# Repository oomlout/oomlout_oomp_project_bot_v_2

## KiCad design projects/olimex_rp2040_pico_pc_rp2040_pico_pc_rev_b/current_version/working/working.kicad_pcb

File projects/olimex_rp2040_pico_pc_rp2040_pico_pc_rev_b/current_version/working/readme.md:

# rp2040_pico_pc
 
## summary 
* id: olimex_rp2040_pico_pc_rp2040_pico_pc_rev_b
* user: olimex
* name: rp2040_pico_pc
* board: rp2040_pico_pc_rev_b
* repo: https://github.com/OLIMEX/RP2040-PICO-PC
* src_file_repo_kicad_pcb: HARDWARE/RP2040-PICO-PC hardware revision B/RP2040-PICO-PC_rev_B.kicad_pcb
* src_file_repo_kicad_pcb_link: https://github.com/OLIMEX/RP2040-PICO-PC/tree/main/HARDWARE/RP2040-PICO-PC hardware revision B/RP2040-PICO-PC_rev_B.kicad_pcb

* src_file_repo_sch: HARDWARE/RP2040-PICO-PC hardware revision B/RP2040-PICO-PC_rev_B.sch
* src_file_repo_sch_link: https://github.com/OLIMEX/RP2040-PICO-PC/tree/main/HARDWARE/RP2040-PICO-PC hardware revision B/RP2040-PICO-PC_rev_B.sch
* full details link: https://github.com/oomlout/oomlout_oomp_project_bot_v_2/tree/main/projects/olimex_rp2040_pico_pc_rp2040_pico_pc_rev_b/current_version/working

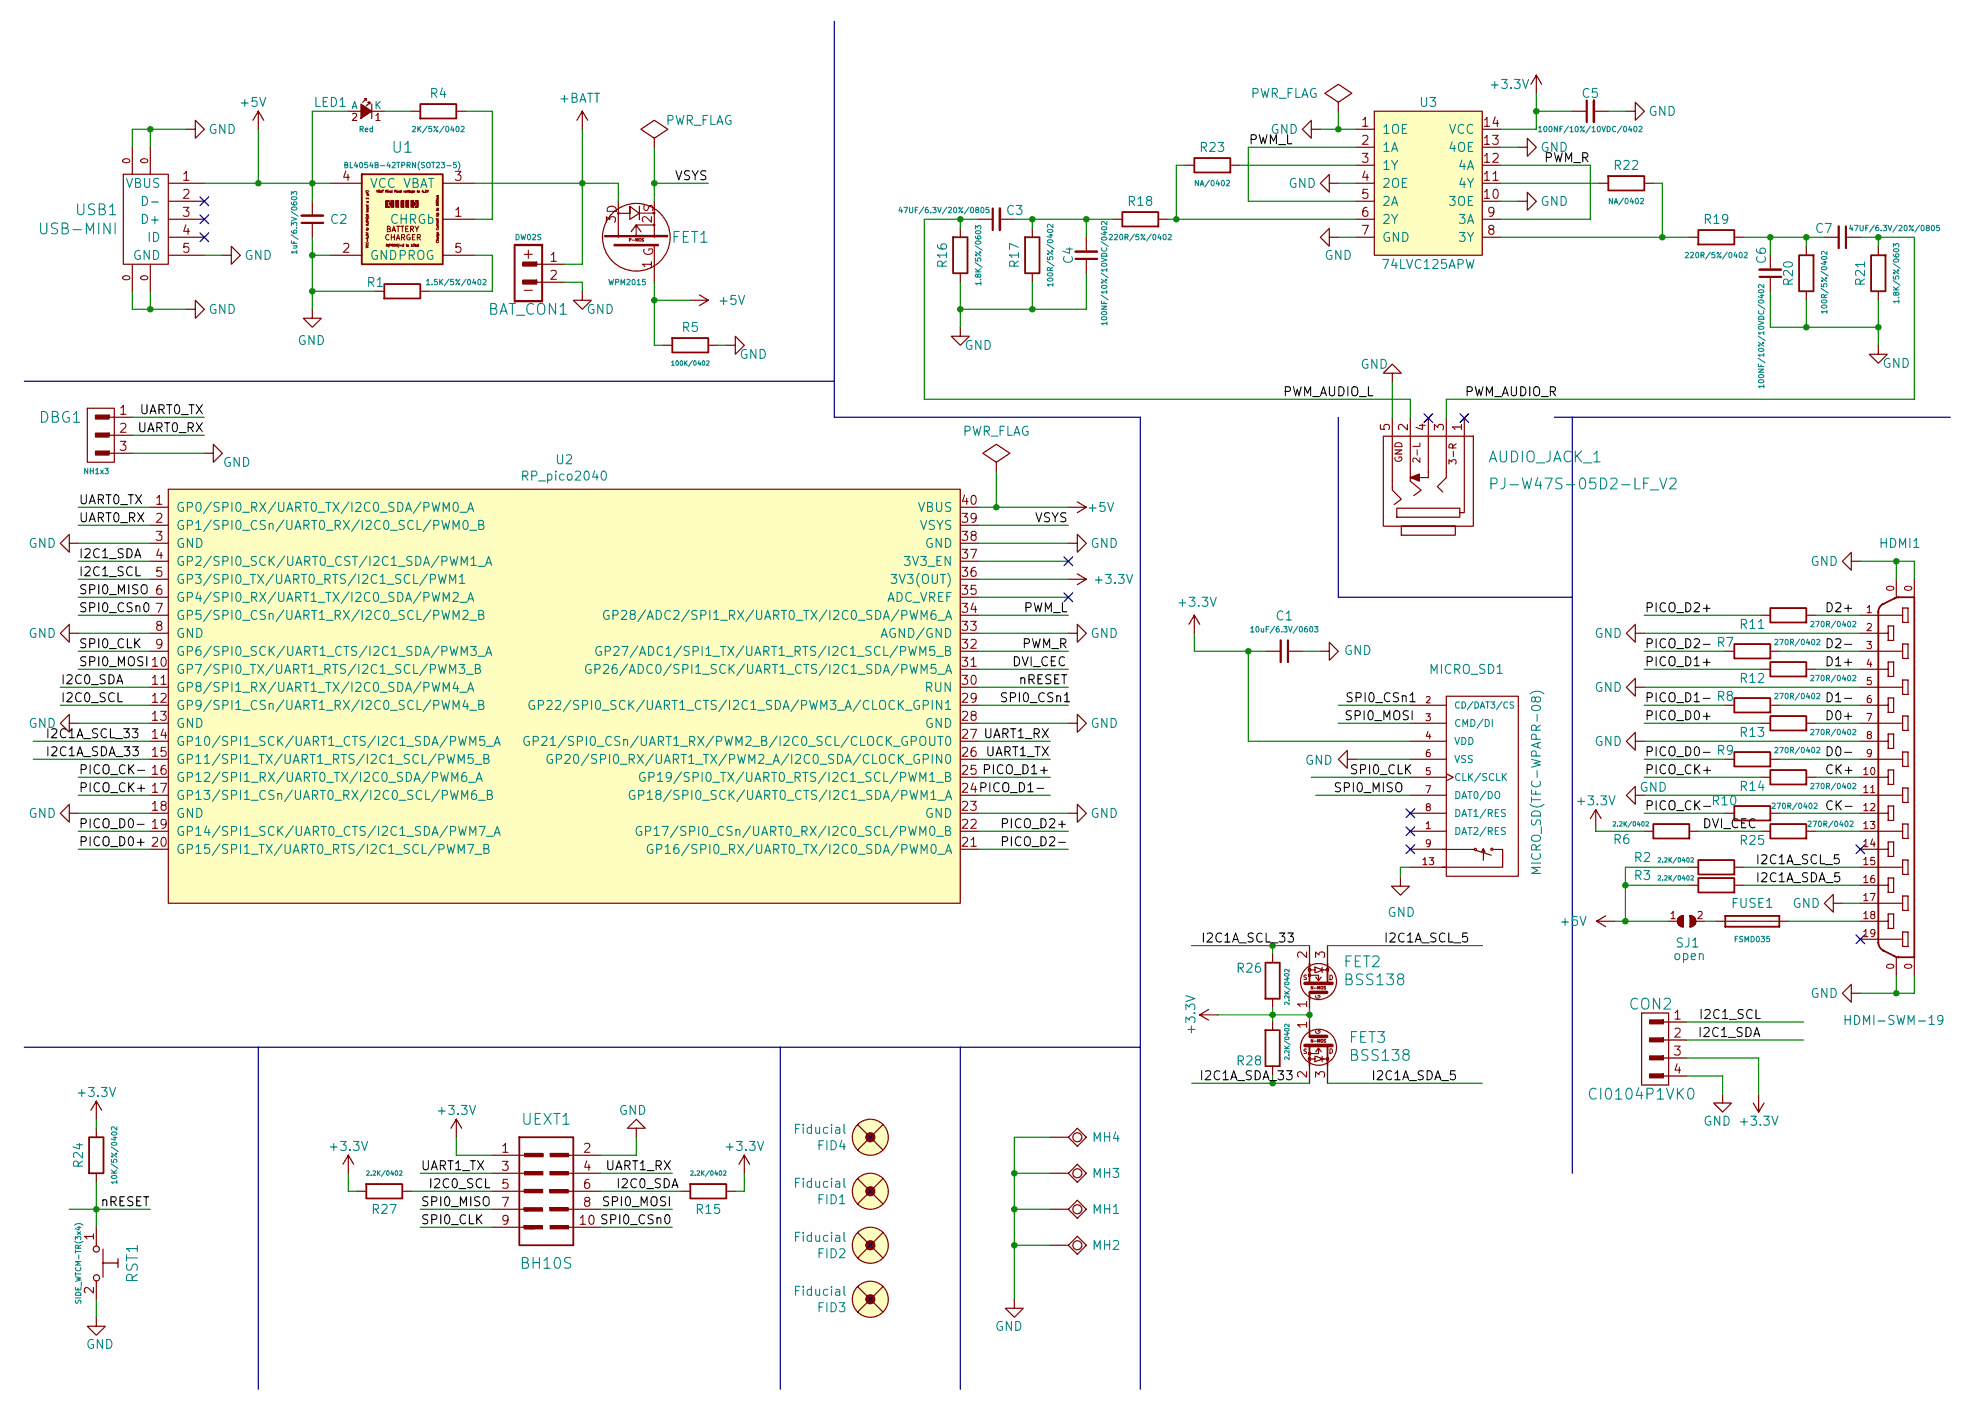
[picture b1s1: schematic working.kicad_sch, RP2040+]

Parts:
AUDIO_JACK_1: PJ-W47S-05D2-LF_V2; PJ-W47S-05D2-LF_5PIN_V2
BAT_CON1: DW02S; LIPO_BAT_VERTICAL_DW02S
C1: 10uF/6.3V/0603; C_0603_5MIL_DWS
C2: 1uF/6.3V/0603; C_0603_5MIL_DWS
C3, C7: 47UF/6.3V/20%/0805; C_0805_5MIL_DWS
C4, C5, C6: 100NF/10%/10VDC/0402; C_0402_5MIL_DWS
CON2: CI0104P1VK0; CL0104PV1K0
DBG1: NH1x3; HN1x3
FET1: WPM2015; SOT23
FET2, FET3: BSS138; SOT23
FID1, FID2, FID3, FID4: Fiducial; Fiducial1x3
FUSE1: FSMD035; FUSE-1206
HDMI1: HDMI-SWM-19; HDMI-SWM-19-TEST
LED1: Red; LED_0603_KA
MH1, MH2, MH3, MH4: Mounting_hole_Shield_3.3mm
MICRO_SD1: MICRO_SD(TFC-WPAPR-08); TFC-WPAPR-08
R1: 1.5K/5%/0402; R_0402_5MIL_DWS
R2, R3, R6, R15, R26, R27, R28: 2.2K/0402; R_0402_5MIL_DWS
R4: 2K/5%/0402; R_0402_5MIL_DWS
R5: 100K/0402; R_0402_5MIL_DWS
R7, R8, R9, R10, R11, R12, R13, R14, R25: 270R/0402; R_0402_5MIL_DWS
R16, R21: 1.8K/5%/0603; R_0603_5MIL_DWS
R17, R20: 100R/5%/0402; R_0402_5MIL_DWS
R18, R19: 220R/5%/0402; R_0402_5MIL_DWS
R22, R23: NA/0402; R_0402_5MIL_DWS
R24: 10K/5%/0402; R_0402_5MIL_DWS
RST1: SIDE_WTCM-TR(3x4); TSW34-W16PR-220
SJ1: open; SJ_1_SMALLER
U1: BL4054B-42TPRN(SOT23-5); SOT-23-5
U2: RP_pico2040; RP_Pico2040
U3: 74LVC125APW; 74LVC125A(TSSOP14-14_leads-4.4mm_body_width-SOT402-1)
UEXT1: BH10S
USB1: USB-MINI; USB-MICRO_MISB-SWMM-5B_LF

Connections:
+3V3: C1.2, C5.1, CON2.3, FET2.1 (G), FET3.1 (G), MICRO_SD1.4 (VDD), R6.1, R15.1, R24.1, R26.2, R27.2, R28.2, U2.36 (3V3(OUT)), U3.14 (VCC), UEXT1.1
+5V: C2.2, FET1.1, LED1.2 (A), R2.1, R3.1, R5.2, SJ1.1, U1.4 (VCC), U2.40 (VBUS), USB1.1 (VBUS)
+BATT: BAT_CON1.1, FET1.3, U1.3 (VBAT)
/CK+: HDMI1.10, R14.2
/CK-: HDMI1.12, R10.2
/D0+: HDMI1.7, R13.2
/D0-: HDMI1.9, R9.2
/D1+: HDMI1.4, R12.2
/D1-: HDMI1.6, R8.2
/D2+: HDMI1.1, R11.2
/D2-: HDMI1.3, R7.2
/DVI_CEC: R6.2, R25.1, U2.31 (GP26/ADC0/SPI1_SCK/UART1_CTS/I2C1_SDA/P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)
/I2C0_SCL: R27.1, U2.12 (GP9/SPI1_CSn/UART1_RX/I2C0_SCL/PWM4_B), UEXT1.5
/I2C0_SDA: R15.2, U2.11 (GP8/SPI1_RX/UART1_TX/I2C0_SDA/PWM4_A), UEXT1.6
/I2C1A_SCL_5: FET2.3 (D), HDMI1.15, R2.2
/I2C1A_SCL_33: FET2.2 (S), R26.1, U2.14 (GP10/SPI1_SCK/UART1_CTS/I2C1_SDA/PWM5_A)
/I2C1A_SDA_5: FET3.3 (D), HDMI1.16, R3.2
/I2C1A_SDA_33: FET3.2 (S), R28.1, U2.15 (GP11/SPI1_TX/UART1_RTS/I2C1_SCL/PWM5_B)
/I2C1_SCL: CON2.1, U2.5 (GP3/SPI0_TX/UART0_RTS/I2C1_SCL/PWM1)
/I2C1_SDA: CON2.2, U2.4 (GP2/SPI0_SCK/UART0_CST/I2C1_SDA/PWM1_A)
/PICO_CK+: R14.1, U2.17 (GP13/SPI1_CSn/UART0_RX/I2C0_SCL/PWM6_B)
/PICO_CK-: R10.1, U2.16 (GP12/SPI1_RX/UART0_TX/I2C0_SDA/PWM6_A)
/PICO_D0+: R13.1, U2.20 (GP15/SPI1_TX/UART0_RTS/I2C1_SCL/PWM7_B)
/PICO_D0-: R9.1, U2.19 (GP14/SPI1_SCK/UART0_CTS/I2C1_SDA/PWM7_A)
/PICO_D1+: R12.1, U2.25 (GP19/SPI0_TX/UART0_RTS/I2C1_SCL/PWM1_B)
/PICO_D1-: R8.1, U2.24 (GP18/SPI0_SCK/UART0_CTS/I2C1_SDA/PWM1_A)
/PICO_D2+: R11.1, U2.22 (GP17/SPI0_CSn/UART0_RX/I2C0_SCL/PWM0_B)
/PICO_D2-: R7.1, U2.21 (GP16/SPI0_RX/UART0_TX/I2C0_SDA/PWM0_A)
/PWM_AUDIO_L: AUDIO_JACK_1.2, C3.1, R16.2
/PWM_AUDIO_R: AUDIO_JACK_1.3, C7.1, R21.2
/PWM_L: U2.34 (GP28/ADC2/SPI1_RX/UART0_TX/I2C0_SDA/PWM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), U3.2 (1A), U3.5 (2A)
/PWM_R: U2.32 (GP27/ADC1/SPI1_TX/UART1_RTS/I2C1_SCL/PW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), U3.9 (3A), U3.12 (4A)
/SPI0_CLK: MICRO_SD1.5 (CLK/SCLK), U2.9 (GP6/SPI0_SCK/UART1_CTS/I2C1_SDA/PWM3_A), UEXT1.9
/SPI0_CSn0: U2.7 (GP5/SPI0_CSn/UART1_RX/I2C0_SCL/PWM2_B), UEXT1.10
/SPI0_CSn1: MICRO_SD1.2 (CD/DAT3/CS), U2.29 (GP22/SPI0_SCK/UART1_CTS/I2C1_SDA/PWM3_A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)
/SPI0_MISO: MICRO_SD1.7 (DAT0/DO), U2.6 (GP4/SPI0_RX/UART1_TX/I2C0_SDA/PWM2_A), UEXT1.7
/SPI0_MOSI: MICRO_SD1.3 (CMD/DI), U2.10 (GP7/SPI0_TX/UART1_RTS/I2C1_SCL/PWM3_B), UEXT1.8
/UART0_RX: DBG1.2, U2.2 (GP1/SPI0_CSn/UART0_RX/I2C0_SCL/PWM0_B)
/UART0_TX: DBG1.1, U2.1 (GP0/SPI0_RX/UART0_TX/I2C0_SDA/PWM0_A)
/UART1_RX: U2.27 (GP21/SPI0_CSn/UART1_RX/PWM2_B/I2C0_SCL/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), UEXT1.4
/UART1_TX: U2.26 (GP20/SPI0_RX/UART1_TX/PWM2_A/I2C0_SDA/C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), UEXT1.3
/VSYS: FET1.2, U2.39 (VSYS)
/nRESET: R24.2, RST1.1, U2.30 (RUN)
GND: AUDIO_JACK_1.5, BAT_CON1.2, C1.1, C2.1, C4.1, C5.2, C6.1, CON2.4, DBG1.3, HDMI1.0 (20), HDMI1.2, HDMI1.5, HDMI1.8, HDMI1.11, HDMI1.17, MH1.GND1, MH2.GND1, MH3.GND1, MH4.GND1, MICRO_SD1.6 (VSS), MICRO_SD1.10, MICRO_SD1.11, MICRO_SD1.12, MICRO_SD1.13, R1.2, R5.1, R16.1, R17.1, R20.1, R21.1, RST1.2, U1.2 (GND), U2.3 (GND), U2.8 (GND), U2.13 (GND), U2.18 (GND), U2.23 (GND), U2.28 (GND), U2.33 (AGND/GND), U2.38 (GND), U3.1 (1OE), U3.4 (2OE), U3.7 (GND), U3.10 (3OE), U3.13 (4OE), UEXT1.2, USB1.0, USB1.5 (GND)
unnamed: C3.2, C4.2, R17.2, R18.1
unnamed: C6.2, C7.2, R19.1, R20.2
unnamed: FUSE1.1, SJ1.2
unnamed: FUSE1.2, HDMI1.18
unnamed: HDMI1.13, R25.2
unnamed: LED1.1 (K), R4.2
unnamed: R1.1, U1.5 (PROG)
unnamed: R4.1, U1.1 (CHRGb)
unnamed: R18.2, R23.1, U3.6 (2Y)
unnamed: R19.2, R22.1, U3.8 (3Y)
unnamed: R22.2, U3.11 (4Y)
unnamed: R23.2, U3.3 (1Y)

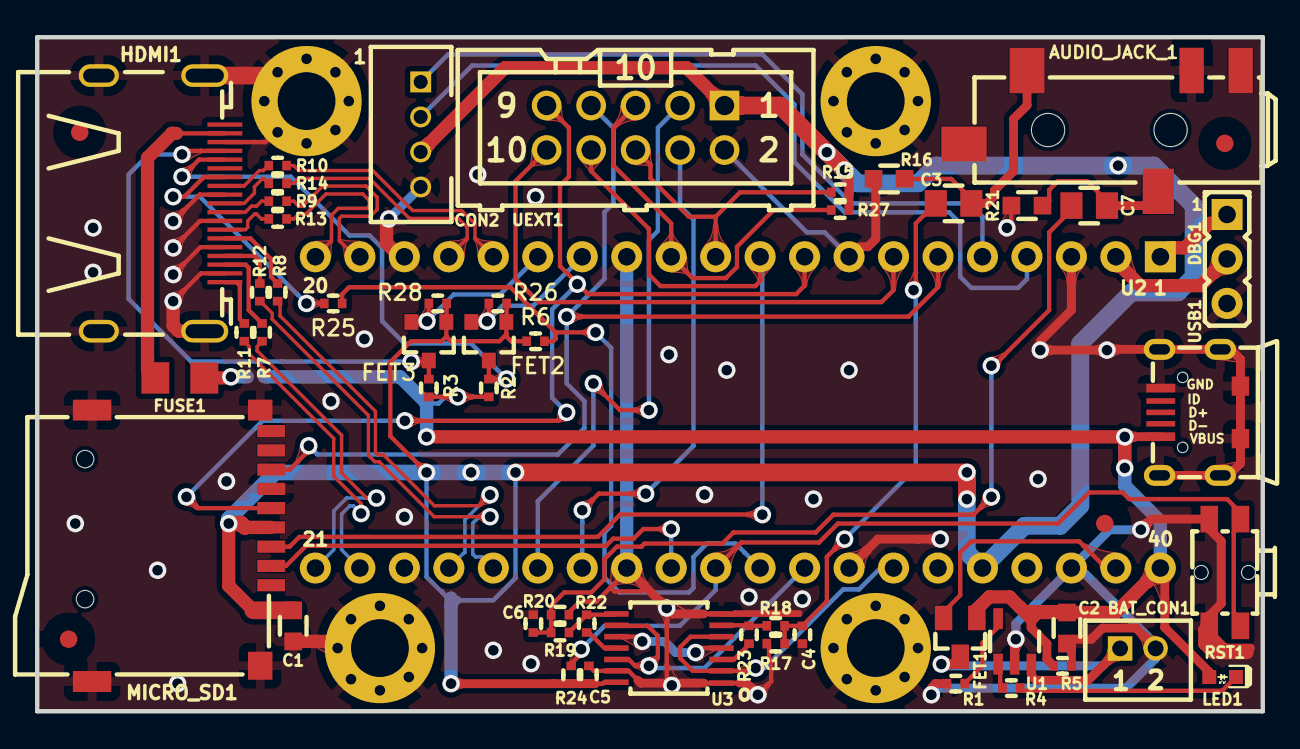
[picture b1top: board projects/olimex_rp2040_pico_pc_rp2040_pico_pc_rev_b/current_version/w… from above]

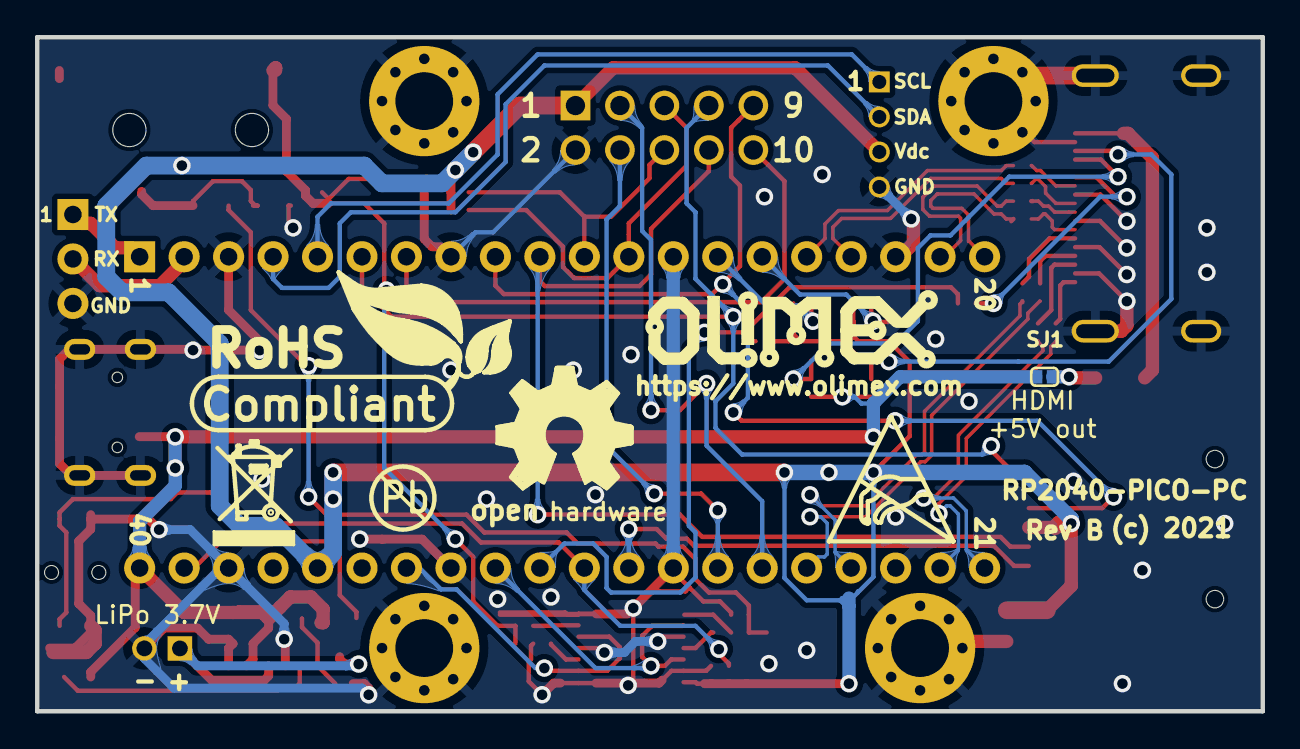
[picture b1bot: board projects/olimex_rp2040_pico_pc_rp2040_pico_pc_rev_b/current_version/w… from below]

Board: 2 copper layers, 70.0 x 38.5 mm, 67 parts (7 on the bottom side), 56 nets.

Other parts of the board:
Antistatic: Logo; LOGO_ANTISTATIC_1
OLIMEX_LOGO: Logo; OLIMEX_LOGO_TB
Open_Hardware: Logo; LOGO_OPENHARDWARE_8x8
PB_FREE: Logo; LOGO_PBFREE
Recycle_bin: logo; LOGO_RECYCLEBIN_1
RoHS_Complaint: Logo; LOGO_ROHS_1

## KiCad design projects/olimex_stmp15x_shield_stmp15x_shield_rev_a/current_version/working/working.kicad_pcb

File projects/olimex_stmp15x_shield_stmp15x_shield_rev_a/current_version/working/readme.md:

# stmp15x_shield
 
## summary 
* id: olimex_stmp15x_shield_stmp15x_shield_rev_a
* user: olimex
* name: stmp15x_shield
* board: stmp15x_shield_rev_a
* repo: https://github.com/OLIMEX/STMP15X-SHIELD
* src_file_repo_kicad_pcb: HARDWARE/STMP15x-SHIELD_Rev_A/STMP15x-SHIELD_Rev_A.kicad_pcb
* src_file_repo_kicad_pcb_link: https://github.com/OLIMEX/STMP15X-SHIELD/tree/main/HARDWARE/STMP15x-SHIELD_Rev_A/STMP15x-SHIELD_Rev_A.kicad_pcb

* src_file_repo_brd: HARDWARE/STMP15x-SHIELD_Rev_A/Extensions/A10-A20-OLINUXINO-MICRO_Extension_Rev_A_STMP15x-SHIELD_GPIO1_EXTENSION.brd
* src_file_repo_brd_link: https://github.com/OLIMEX/STMP15X-SHIELD/tree/main/HARDWARE/STMP15x-SHIELD_Rev_A/Extensions/A10-A20-OLINUXINO-MICRO_Extension_Rev_A_STMP15x-SHIELD_GPIO1_EXTENSION.brd
* src_file_repo_sch: HARDWARE/STMP15x-SHIELD_Rev_A/STMP15x-SHIELD_Rev_A.sch
* src_file_repo_sch_link: https://github.com/OLIMEX/STMP15X-SHIELD/tree/main/HARDWARE/STMP15x-SHIELD_Rev_A/STMP15x-SHIELD_Rev_A.sch
* full details link: https://github.com/oomlout/oomlout_oomp_project_bot_v_2/tree/main/projects/olimex_stmp15x_shield_stmp15x_shield_rev_a/current_version/working

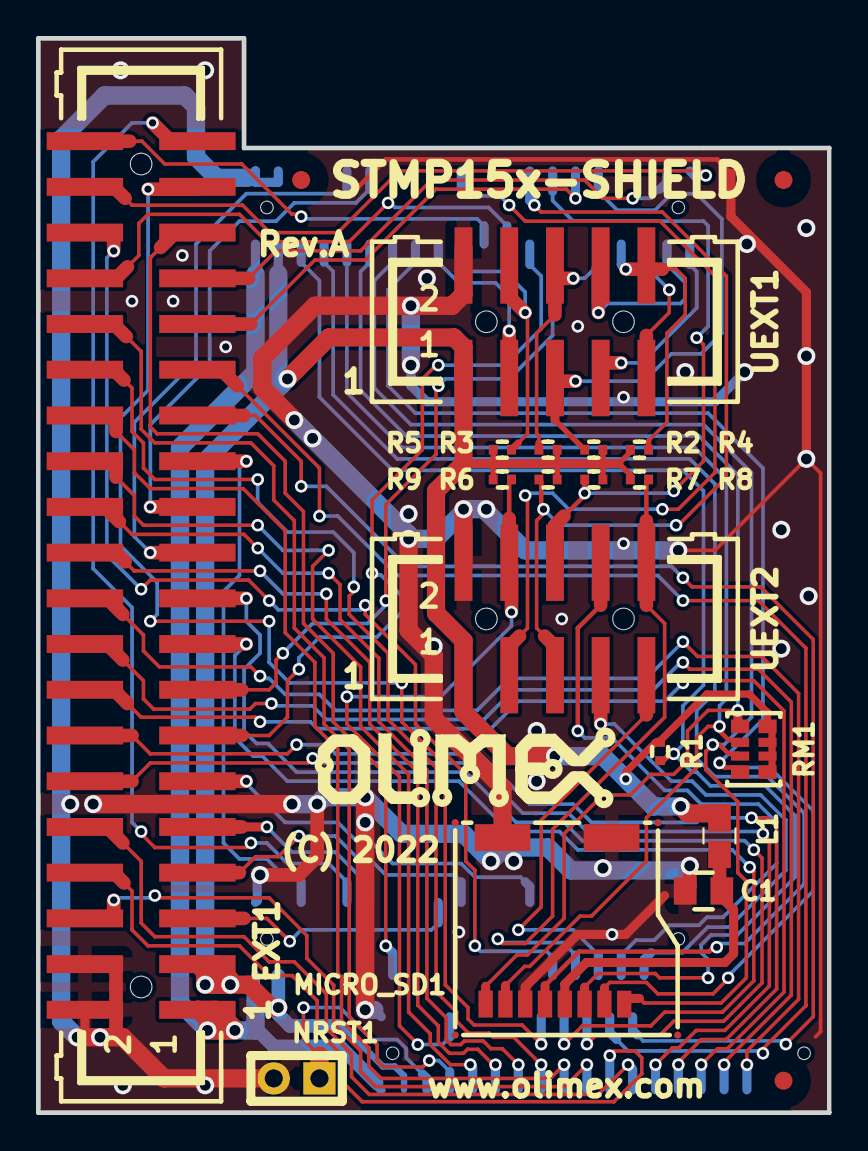
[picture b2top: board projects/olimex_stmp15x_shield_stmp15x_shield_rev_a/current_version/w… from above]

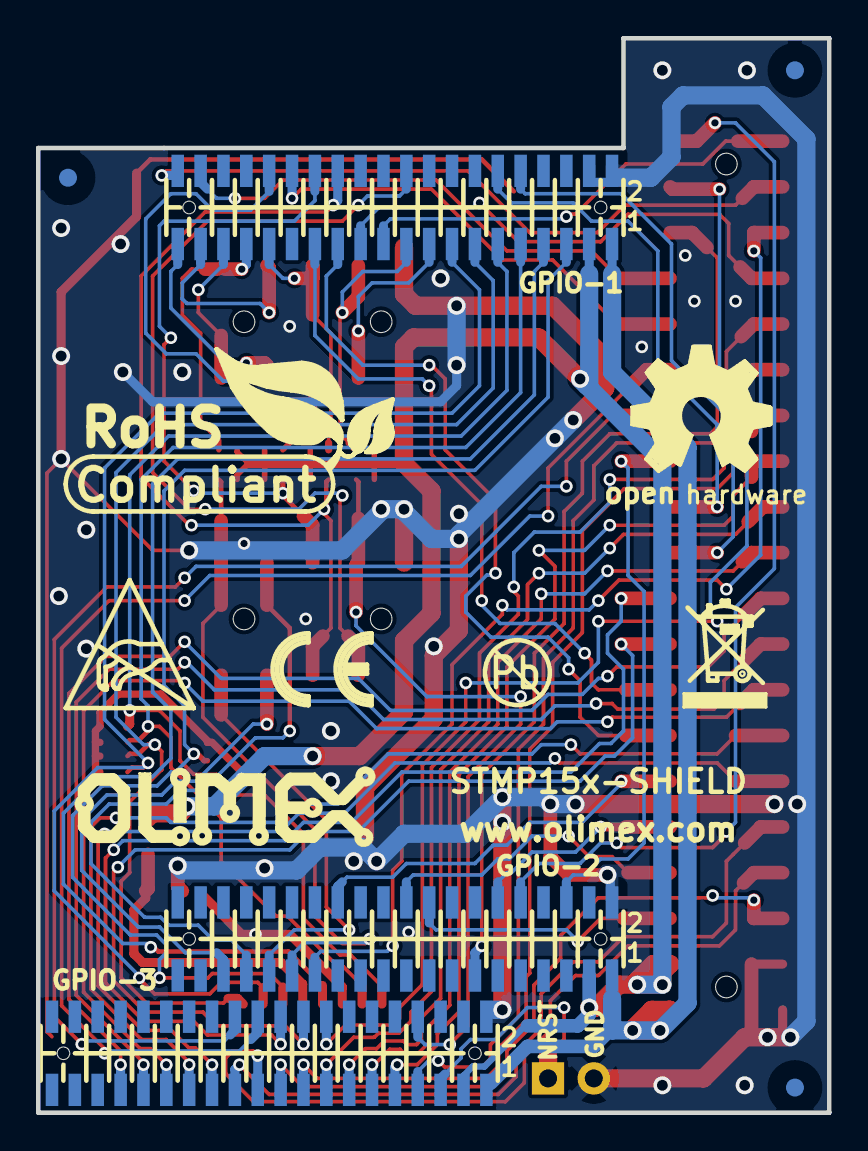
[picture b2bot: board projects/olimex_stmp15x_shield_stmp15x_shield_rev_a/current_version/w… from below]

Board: 2 copper layers, 43.9 x 59.7 mm, 34 parts (13 on the bottom side), 63 nets.

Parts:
C1: 47uF/6.3V/20%/X5R/C0805; C_0805_5MIL_DWS
EXT1: P-B-V-40-LF; GBH-254-SMT-40
FID1, FID2, FID3, FID4, FID5, FID6: Fiducial; Fiducial1x3
GPIO-1, GPIO-2, GPIO-3: YA-V36P-2X20-LF; GPCB127SMT-02X20(YA-V36P-2X20-LF)
L1: FB0805/600R/2A; L_0805_5MIL_DWS
Logo_OSHW: LOGO_OPENHARDWARE_8x8
Logo_Olimex_1, Logo_Olimex_2: OLIMEX_LOGO_TB
MICRO_SD1: TFC-WXCP11-08-LF
NRST1: NA(HN1x2); HN1x2_Jumper
R1, R4, R5, R8, R9: 10k/R0402; R_0402_5MIL_DWS
R2: NA(2.2k/R0402); R_0402_5MIL_DWS
R3, R6, R7: 2.2k/R0402; R_0402_5MIL_DWS
RM1: RA1206_(4x0603)_4B8_100k; RA1206_(4X0603)_4B8_xx
Sign_Antistatic: LOGO_ANTISTATIC_1
Sign_CE: CE_Sign
Sign_PB-Free: LOGO_PBFREE
Sign_RecycleBin: LOGO_RECYCLEBIN_1
Sign_RoHS: LOGO_ROHS_1
UEXT1, UEXT2: P-B-V-10-LF; GBH-254-SMT-10

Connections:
+3V3: EXT1.3, GPIO-1.3, GPIO-2.3, GPIO-3.3, L1.1, R1.2, R2.1, R3.1, R4.1, R5.1, R6.1, R7.1, R8.1, R9.1, RM1.1.1, RM1.2.1, RM1.3.1, RM1.4.1, UEXT1.1, UEXT2.1
+5V: EXT1.1, GPIO-1.1, GPIO-2.1, GPIO-3.1
/NRST: GPIO-3.5, NRST1.1
/PA4\SPI1(3)(6)_NSS: EXT1.21, GPIO-1.10
/PA5\SPI1(6)_SCK: EXT1.23, GPIO-1.12
/PA6\SPI1(6)_MISO: EXT1.25, GPIO-2.6
/PB5\SPDIF_TX\SPI1(3)(6)_MOSI\UART5_RX\CAN2_RX: EXT1.27, GPIO-3.24
/PB7\I2C1(4)_SDA\USART1_RX: EXT1.9, GPIO-2.12
/PB8\I2C1(4)_SCL\UART4_RX: EXT1.11, GPIO-2.26
/PB10\USART3_TX\I2C2_SCL\SPI2_SCK: EXT1.13, GPIO-1.25
/PB12\USART3_RX\UART5_RX\SPI2_NSS\CAN2_RX: EXT1.15, GPIO-1.27
/PB13\SPI2_SCK\USART3_CTS\UART5_TX\CAN2_TX: EXT1.17, GPIO-3.18
/PC3\SPI2_MOSI: EXT1.19, GPIO-3.20
/PD0\NAND-DQ2\I2C5(6)_SDA\UART4_RX\CAN1_RX: EXT1.10, GPIO-3.23
/PD1\NAND-DQ3\I2C5(6)_SCL\UART4_TX\CAN1_TX: EXT1.12, GPIO-3.25
/PD4\NAND-RE\USART2_RTS: EXT1.26, GPIO-3.9
/PD5\NAND-WE\USART2_TX: EXT1.22, GPIO-3.11
/PD6\NAND-RB\SPI3_MOSI\USART2_RX: EXT1.24, GPIO-3.13
/PD7\SDMMC3_D3: GPIO-1.15, MICRO_SD1.2, RM1.1.2
/PD8\USART3_TX: GPIO-1.17, UEXT1.3
/PD9\USART3_RX: GPIO-1.19, R5.2, UEXT1.4
/PD11\NAND-CLE\USART3_CTS: EXT1.30, GPIO-3.15
/PD12\NAND-ALE\I2C1(4)_SCL\USART3_RTS: EXT1.28, GPIO-3.17
/PD14\NAND-DQ0\UART8_CTS: EXT1.6, GPIO-3.19
/PD15\NAND-DQ1\UART8_CTS: EXT1.8, GPIO-3.21
/PE0\UART8_RX\SPI3_SCK: GPIO-3.8, R9.2, UEXT2.4
/PE1\UART8_TX: GPIO-1.20, UEXT2.3
/PE7\NAND-DQ4\UART7_RX: EXT1.14, GPIO-3.27
/PE8\NAND-DQ5\UART7_TX: EXT1.16, GPIO-3.29
/PE9\NAND-DQ6\UART7_RTS: EXT1.18, GPIO-3.31
/PE10\NAND-DQ7\UART7_CTS: EXT1.20, GPIO-3.33
/PE11\SPI4_NSS: GPIO-1.33, R4.2, UEXT1.10
/PE12\SPI4_SCK: GPIO-1.35, UEXT1.9
/PE13\SPI4_MISO: GPIO-1.39, UEXT1.7
/PE14\SPI4_MOSI\UART8_RTS: GPIO-1.37, UEXT1.8
/PE15\USART2_CTS\UART8_CTS: EXT1.34, GPIO-1.23
/PF0\SDMMC3_D0: GPIO-1.9, MICRO_SD1.7, RM1.3.2
/PF1\SDMMC3_CMD: GPIO-1.5, MICRO_SD1.3, R1.1
/PF4\SDMMC3_D1: GPIO-1.11, MICRO_SD1.8, RM1.4.2
/PF5\SDMMC3_D2: GPIO-1.13, MICRO_SD1.1, RM1.2.2
/PF11\SPI5_MOSI: EXT1.37, GPIO-3.16
/PG7\UART8_RTS: EXT1.36, GPIO-2.27
/PG8\USART3(6)_RTS\SPI6_NSS: EXT1.40, GPIO-1.21
/PG9\NAND-CE\USART6_RX: EXT1.32, GPIO-3.7
/PG12\SPI6_MISO\USART6_RTS: EXT1.29, GPIO-3.22
/PG15\SDMMC3_CK: GPIO-1.7, MICRO_SD1.5
/PH4\I2C2_SCL: GPIO-1.32, R2.2, UEXT1.5
/PH5\I2C2_SDA\SPI5_NSS: EXT1.31, GPIO-1.30
/PH6\SPI5_SCK: EXT1.33, GPIO-1.38
/PH7\I2C3_SCL\SPI5_MISO: EXT1.35, GPIO-2.13
/PH8\I2C3_SDA: EXT1.39, GPIO-2.10
/PH11\I2C1(4)_SCL: EXT1.5, GPIO-2.18
/PH12\I2C1(4)_SDA: EXT1.7, GPIO-2.20
/PI0\SPI2_NSS: GPIO-2.29, R8.2, UEXT2.10
/PI1\SPI2_SCK: GPIO-2.31, UEXT2.9
/PI2\SPI2_MISO: GPIO-2.35, UEXT2.7
/PI3\SPI2_MOSI: GPIO-2.33, UEXT2.8
/PI10\USART3_CTS: EXT1.38, GPIO-1.40
/PZ1\I2C2(4)(5)(6)_SDA\USART1_RX\SPI1(6)_MISO: GPIO-1.31, R3.2, UEXT1.6
/PZ6\I2C2(6)_SCL\USART1_RX: GPIO-1.26, R6.2, UEXT2.5
/PZ7\I2C2(6)_SDA\USART1_TX: GPIO-1.28, R7.2, UEXT2.6
GND: C1.2, EXT1.2, EXT1.4, GPIO-1.2, GPIO-1.4, GPIO-2.2, GPIO-3.2, MICRO_SD1.6, MICRO_SD1.SH1, MICRO_SD1.SH2, NRST1.2, UEXT1.2, UEXT2.2
unnamed: C1.1, L1.2, MICRO_SD1.4

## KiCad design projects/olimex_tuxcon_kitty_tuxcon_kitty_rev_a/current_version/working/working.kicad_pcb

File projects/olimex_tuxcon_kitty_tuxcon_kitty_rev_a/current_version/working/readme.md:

# tuxcon_kitty
 
## summary 
* id: olimex_tuxcon_kitty_tuxcon_kitty_rev_a
* user: olimex
* name: tuxcon_kitty
* board: tuxcon_kitty_rev_a
* repo: https://github.com/OLIMEX/TuxCon-Kitty
* src_file_repo_kicad_pcb: HARDWARE/REV-A/TuxCon_Kitty_Rev_A.kicad_pcb
* src_file_repo_kicad_pcb_link: https://github.com/OLIMEX/TuxCon-Kitty/tree/master/HARDWARE/REV-A/TuxCon_Kitty_Rev_A.kicad_pcb

* src_file_repo_sch: HARDWARE/REV-A/TuxCon_Kitty_Rev_A.sch
* src_file_repo_sch_link: https://github.com/OLIMEX/TuxCon-Kitty/tree/master/HARDWARE/REV-A/TuxCon_Kitty_Rev_A.sch
* full details link: https://github.com/oomlout/oomlout_oomp_project_bot_v_2/tree/main/projects/olimex_tuxcon_kitty_tuxcon_kitty_rev_a/current_version/working

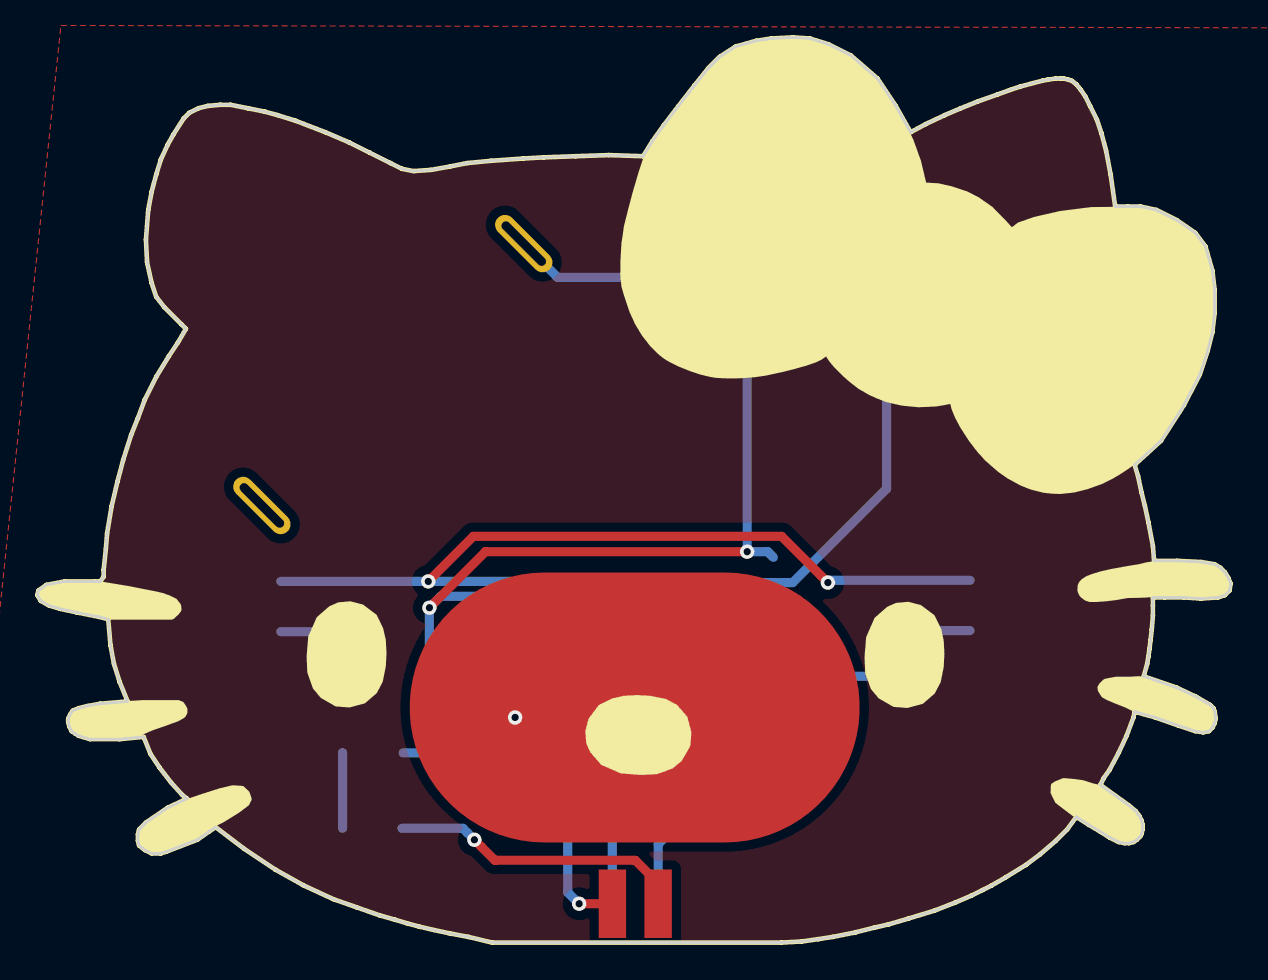
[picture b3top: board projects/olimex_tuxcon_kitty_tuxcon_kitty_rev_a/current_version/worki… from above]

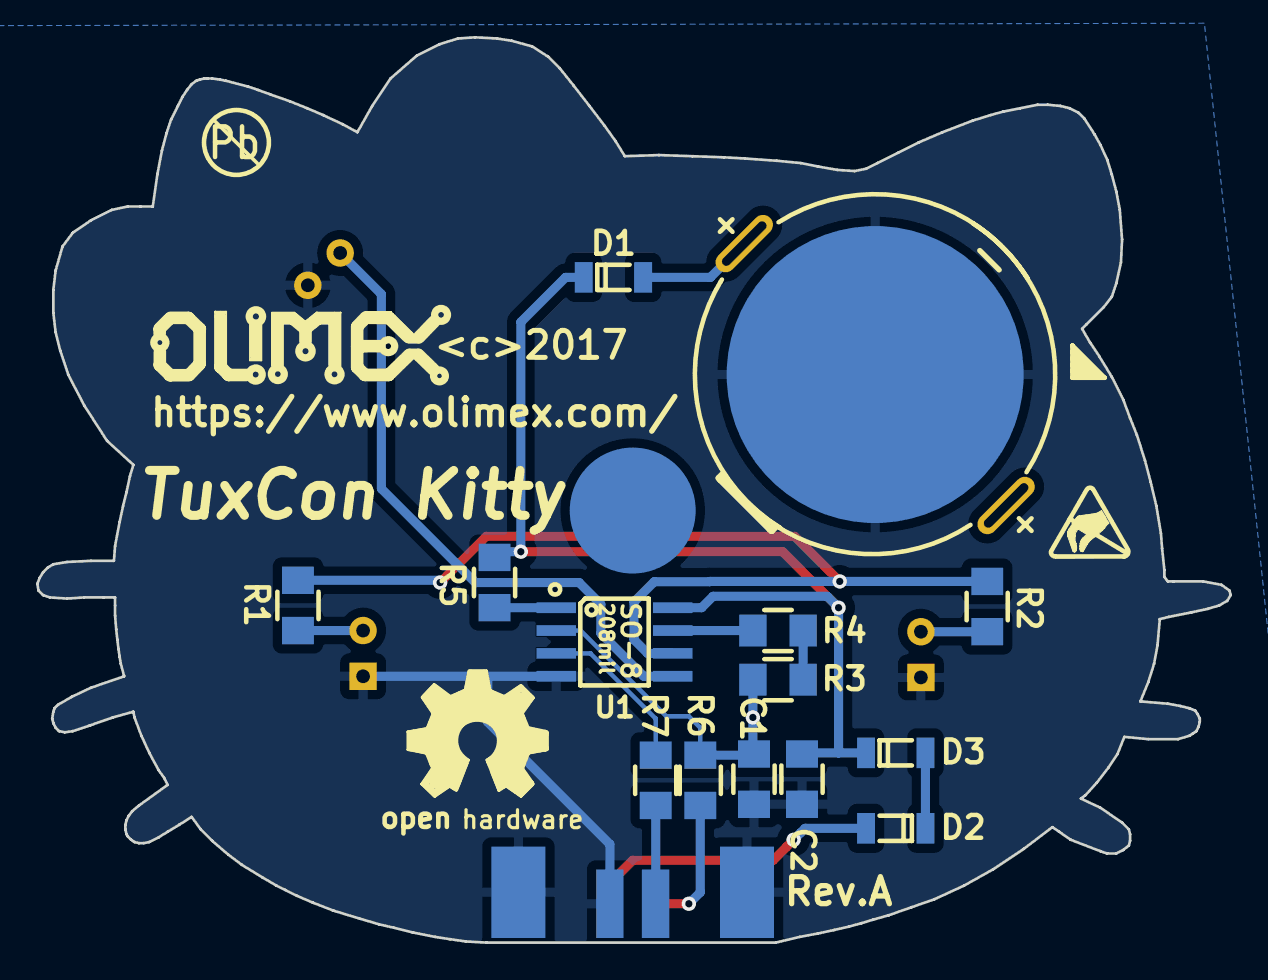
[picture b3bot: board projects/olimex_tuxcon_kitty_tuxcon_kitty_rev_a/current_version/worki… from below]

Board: 2 copper layers, 66.3 x 50.3 mm, 21 parts (16 on the bottom side), 16 nets.

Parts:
BAT1: Battery; CR2032H_PTH
BUZ1: Buzzer_PB1240; MIC
C1: 12pF; C_1206_5MIL_DWS
C2: C_Small; C_1206_5MIL_DWS
D1, D2, D3: 1N4148; SOD80C-4148-KA
LED1, LED2: blue; LED-3mm-PTH-KA
R1, R2: 1K; R_1206_5MIL_DWS
R3, R4: 1M; R_1206_5MIL_DWS
R5: 10K; R_1206_5MIL_DWS
R6, R7: 22R; R_1206_5MIL_DWS
Ref**: Val**; LOGO_ANTISTATIC_SMALL_4.5mmX2.8mm
TESTPAD1, TESTPAD1#2: TESTPAD; TP_SMD_10.00x8.00mm
U1: ATTINY85-20PU; SO-8_208mil
USB1: USB_B; USB-B-EDGE

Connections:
GND: BAT1.2, BUZ1.2, C1.2, C2.2, LED1.1, LED2.1, U1.4, USB1.0, USB1.4
unnamed: BAT1.1, D1.2
unnamed: BUZ1.1, U1.5
unnamed: C1.1, R3.2, R6.1, TESTPAD1.1, U1.2
unnamed: C2.1, D1.1, D3.1, R5.2, U1.8
unnamed: D2.1, D3.2
unnamed: D2.2, USB1.1
unnamed: LED1.2, R1.2
unnamed: LED2.2, R2.2
unnamed: R1.1, R2.1, U1.6
unnamed: R3.1, R4.2
unnamed: R4.1, U1.7
unnamed: R5.1, U1.1
unnamed: R6.2, USB1.2
unnamed: R7.1, U1.3
unnamed: R7.2, USB1.3

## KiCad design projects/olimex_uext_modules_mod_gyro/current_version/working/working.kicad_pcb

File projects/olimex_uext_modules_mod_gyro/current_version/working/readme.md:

# uext_modules
 
## summary 
* id: olimex_uext_modules_mod_gyro
* user: olimex
* name: uext_modules
* board: mod_gyro
* repo: https://github.com/OLIMEX/UEXT-MODULES
* src_file_repo_kicad_pcb: MOD-MPU9150/mod-gyro.kicad_pcb
* src_file_repo_kicad_pcb_link: https://github.com/OLIMEX/UEXT-MODULES/tree/master/MOD-MPU9150/mod-gyro.kicad_pcb

* src_file_repo_sch: MOD-MPU9150/mod-gyro.sch
* src_file_repo_sch_link: https://github.com/OLIMEX/UEXT-MODULES/tree/master/MOD-MPU9150/mod-gyro.sch
* full details link: https://github.com/oomlout/oomlout_oomp_project_bot_v_2/tree/main/projects/olimex_uext_modules_mod_gyro/current_version/working

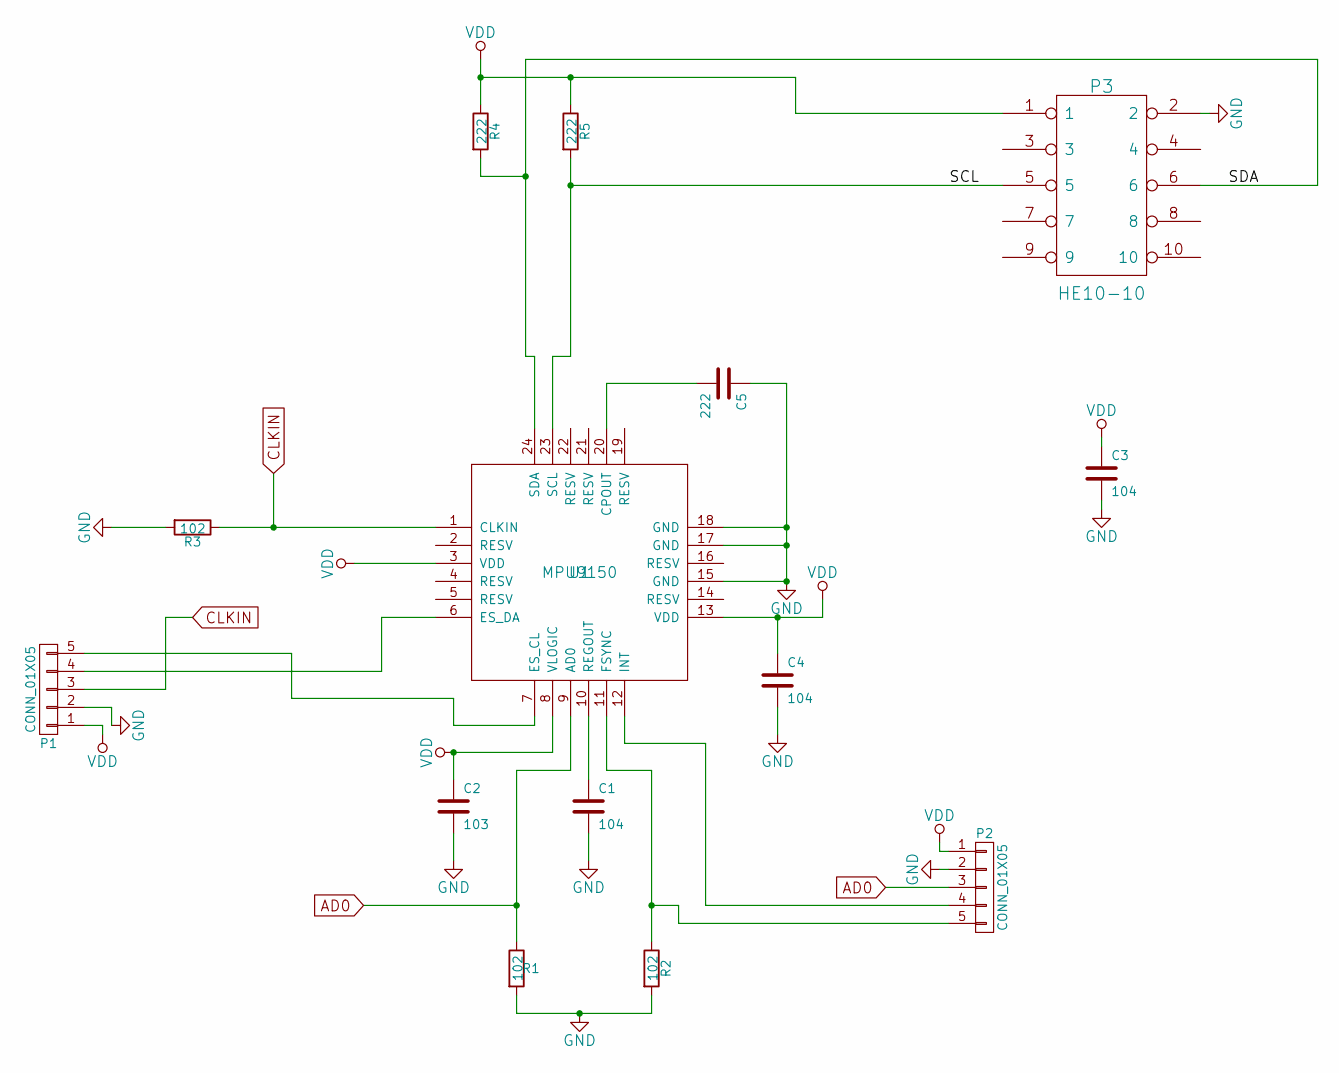
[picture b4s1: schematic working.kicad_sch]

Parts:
C1, C3, C4: 104; C_0603
C2: 103; C_0603
C5: 222; C_0603
P1, P2: CONN_01X05; SIP5_Housing
P3: HE10-10; UEXTF
R1, R2, R3: 102; R_0603
R4, R5: 222; R_0603
U1: MPU9150; QFN-24-1EP_4x4mm_Pitch0.5mm

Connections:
/SCL: P3.5, R5.2, U1.23 (SCL)
/SDA: P3.6, R4.2, U1.24 (SDA)
AD0: P2.3, R1.1, U1.9 (AD0)
CLKIN: P1.3, R3.1, U1.1 (CLKIN)
GND: C1.2, C2.2, C3.2, C4.2, C5.1, P1.2, P2.2, P3.2, R1.2, R2.2, R3.2, U1.15 (GND), U1.17 (GND), U1.18 (GND), U1.25
unnamed: C1.1, U1.10 (REGOUT)
unnamed: C5.2, U1.20 (CPOUT)
unnamed: P1.4, U1.6 (ES_DA)
unnamed: P1.5, U1.7 (ES_CL)
unnamed: P2.4, U1.12 (INT)
unnamed: P2.5, R2.1, U1.11 (FSYNC)
VDD: C2.1, C3.1, C4.1, P1.1, P2.1, P3.1, R4.1, R5.1, U1.3 (VDD), U1.8 (VLOGIC), U1.13 (VDD)

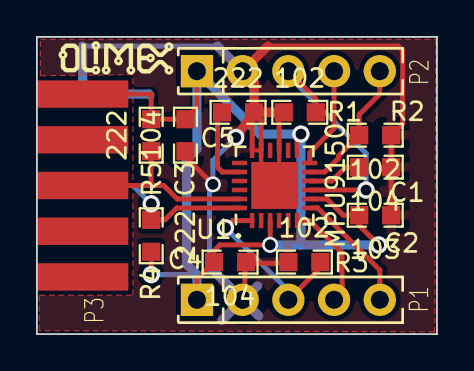
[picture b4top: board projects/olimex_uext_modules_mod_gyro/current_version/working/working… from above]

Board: 2 copper layers, 22.2 x 16.5 mm, 14 parts (0 on the bottom side), 12 nets.

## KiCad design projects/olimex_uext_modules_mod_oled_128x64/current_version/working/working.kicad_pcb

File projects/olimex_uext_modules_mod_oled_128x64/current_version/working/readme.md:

# uext_modules
 
## summary 
* id: olimex_uext_modules_mod_oled_128x64
* user: olimex
* name: uext_modules
* board: mod_oled_128x64
* repo: https://github.com/OLIMEX/UEXT-MODULES
* src_file_repo_kicad_pcb: MOD-OLED-128x64/mod-oled-128x64.kicad_pcb
* src_file_repo_kicad_pcb_link: https://github.com/OLIMEX/UEXT-MODULES/tree/master/MOD-OLED-128x64/mod-oled-128x64.kicad_pcb

* src_file_repo_sch: MOD-OLED-128x64/mod-oled-128x64.sch
* src_file_repo_sch_link: https://github.com/OLIMEX/UEXT-MODULES/tree/master/MOD-OLED-128x64/mod-oled-128x64.sch
* full details link: https://github.com/oomlout/oomlout_oomp_project_bot_v_2/tree/main/projects/olimex_uext_modules_mod_oled_128x64/current_version/working

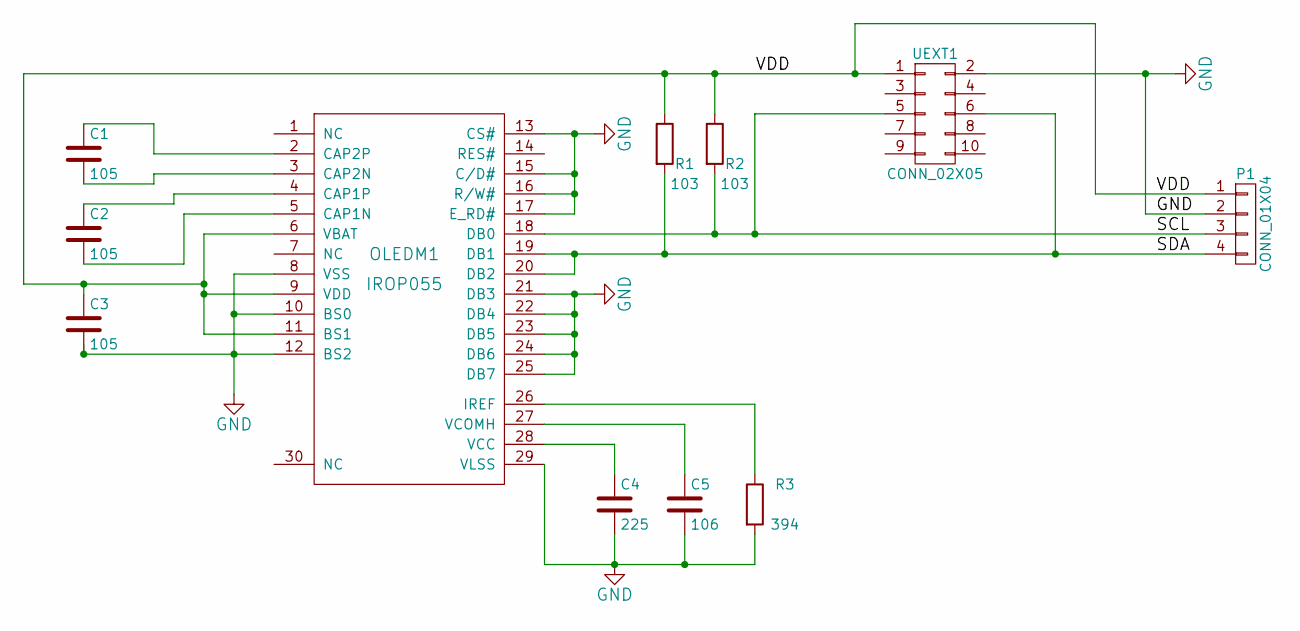
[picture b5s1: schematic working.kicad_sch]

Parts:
C1, C2, C3: 105; C_0603
C4: 225; C_0603
C5: 106; C_0603
OLEDM1: IROP055; IROP055-SSD1306Z-PADS-ONLY
P1: CONN_01X04; SIP4_SMD
R1, R2: 103; R_0603
R3: 394; R_0603
UEXT1: CONN_02X05; UEXTM-SMD

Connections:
/SCL: OLEDM1.18 (DB0), P1.3, R2.2, UEXT1.5
/SDA: OLEDM1.19 (DB1), OLEDM1.20 (DB2), P1.4, R1.2, UEXT1.6
/VDD: C3.1, OLEDM1.6 (VBAT), OLEDM1.9 (VDD), OLEDM1.11 (BS1), P1.1, R1.1, R2.1, UEXT1.1
GND: C3.2, C4.2, C5.2, OLEDM1.8 (VSS), OLEDM1.10 (BS0), OLEDM1.12 (BS2), OLEDM1.13 (CS#), OLEDM1.15 (C/D#), OLEDM1.16 (R/W#), OLEDM1.17 (E_RD#), OLEDM1.21 (DB3), OLEDM1.22 (DB4), OLEDM1.23 (DB5), OLEDM1.24 (DB6), OLEDM1.25 (DB7), OLEDM1.29 (VLSS), P1.2, R3.2, UEXT1.2
unnamed: C1.1, OLEDM1.2 (CAP2P)
unnamed: C1.2, OLEDM1.3 (CAP2N)
unnamed: C2.1, OLEDM1.4 (CAP1P)
unnamed: C2.2, OLEDM1.5 (CAP1N)
unnamed: C4.1, OLEDM1.28 (VCC)
unnamed: C5.1, OLEDM1.27 (VCOMH)
unnamed: OLEDM1.26 (IREF), R3.1

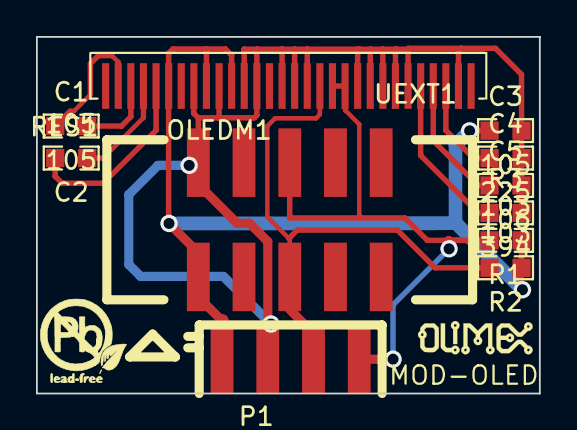
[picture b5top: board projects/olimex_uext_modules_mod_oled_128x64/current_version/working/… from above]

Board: 2 copper layers, 27.9 x 19.8 mm, 12 parts (0 on the bottom side), 11 nets.

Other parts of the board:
RES1: CONN_01X01; TP

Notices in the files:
projects/olimex_rp2040_pico_pc_rp2040_pico_pc_rev_b/current_version/working/working.kicad_pcb:
(c) 2021
projects/olimex_stmp15x_shield_stmp15x_shield_rev_a/current_version/working/working.kicad_pcb:
(C) 2022
projects/olimex_urc_urc_revb/current_version/working/working.kicad_pcb:
(c)2019
